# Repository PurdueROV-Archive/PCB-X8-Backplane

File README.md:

# PCB-X8-Backplane
The board to attach all boards. Note: May not actually be a backplane!
Here is another line!

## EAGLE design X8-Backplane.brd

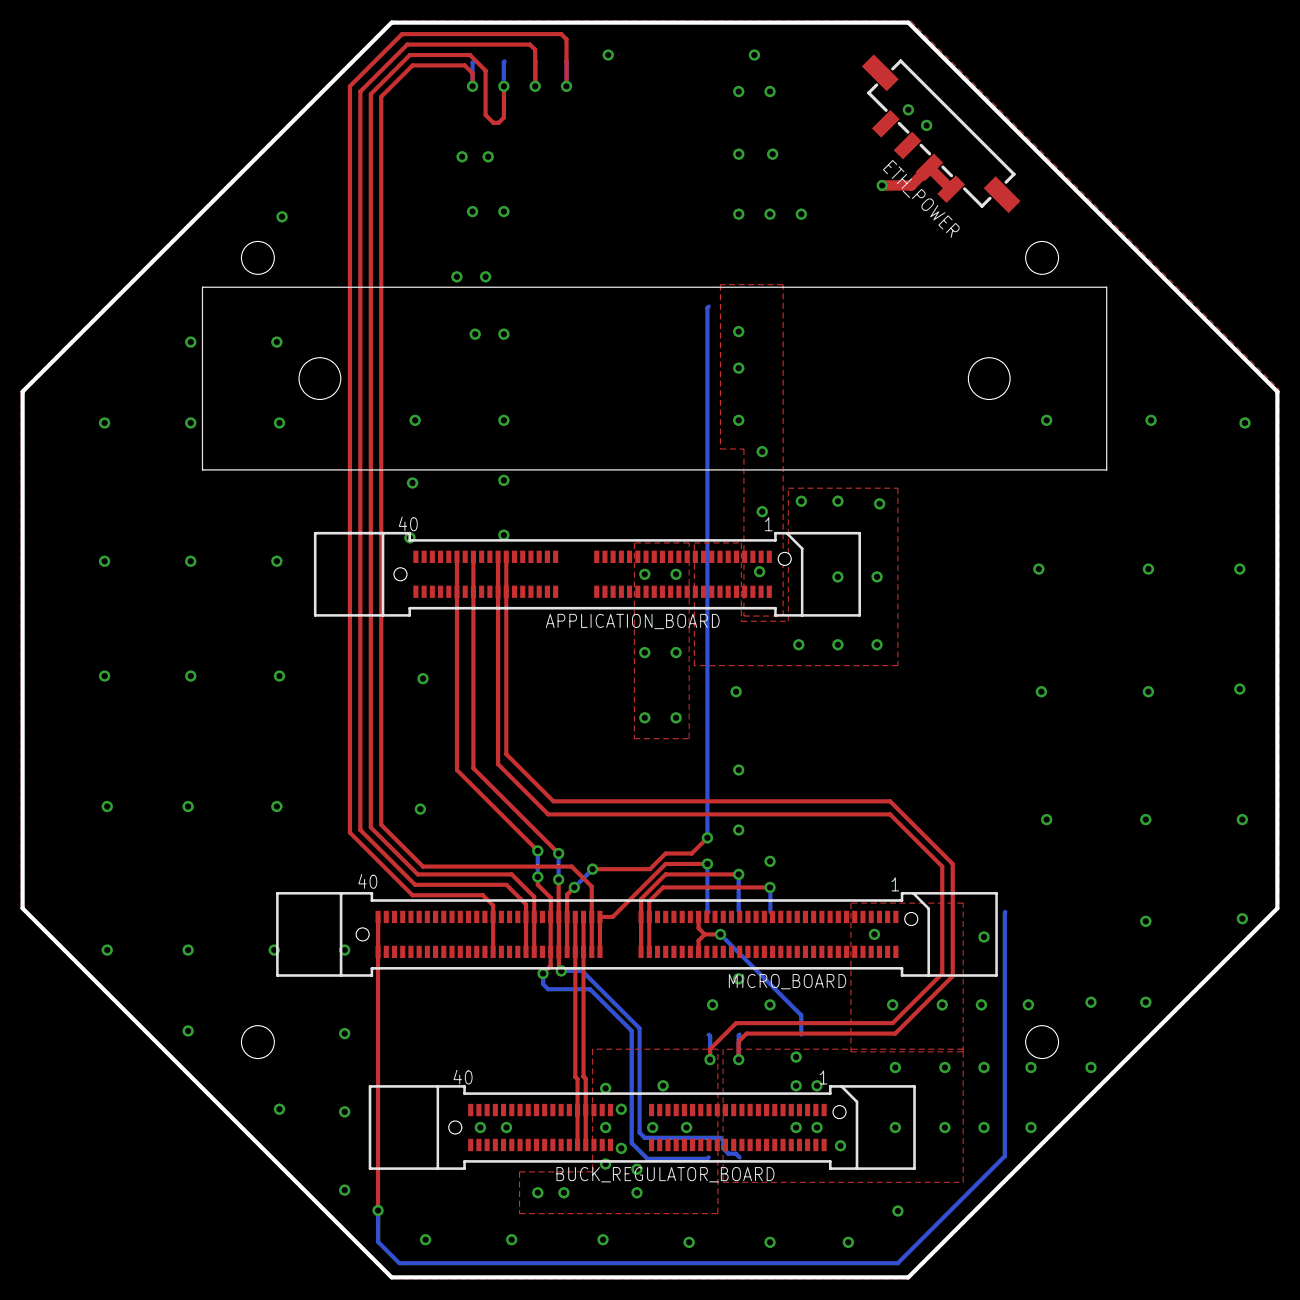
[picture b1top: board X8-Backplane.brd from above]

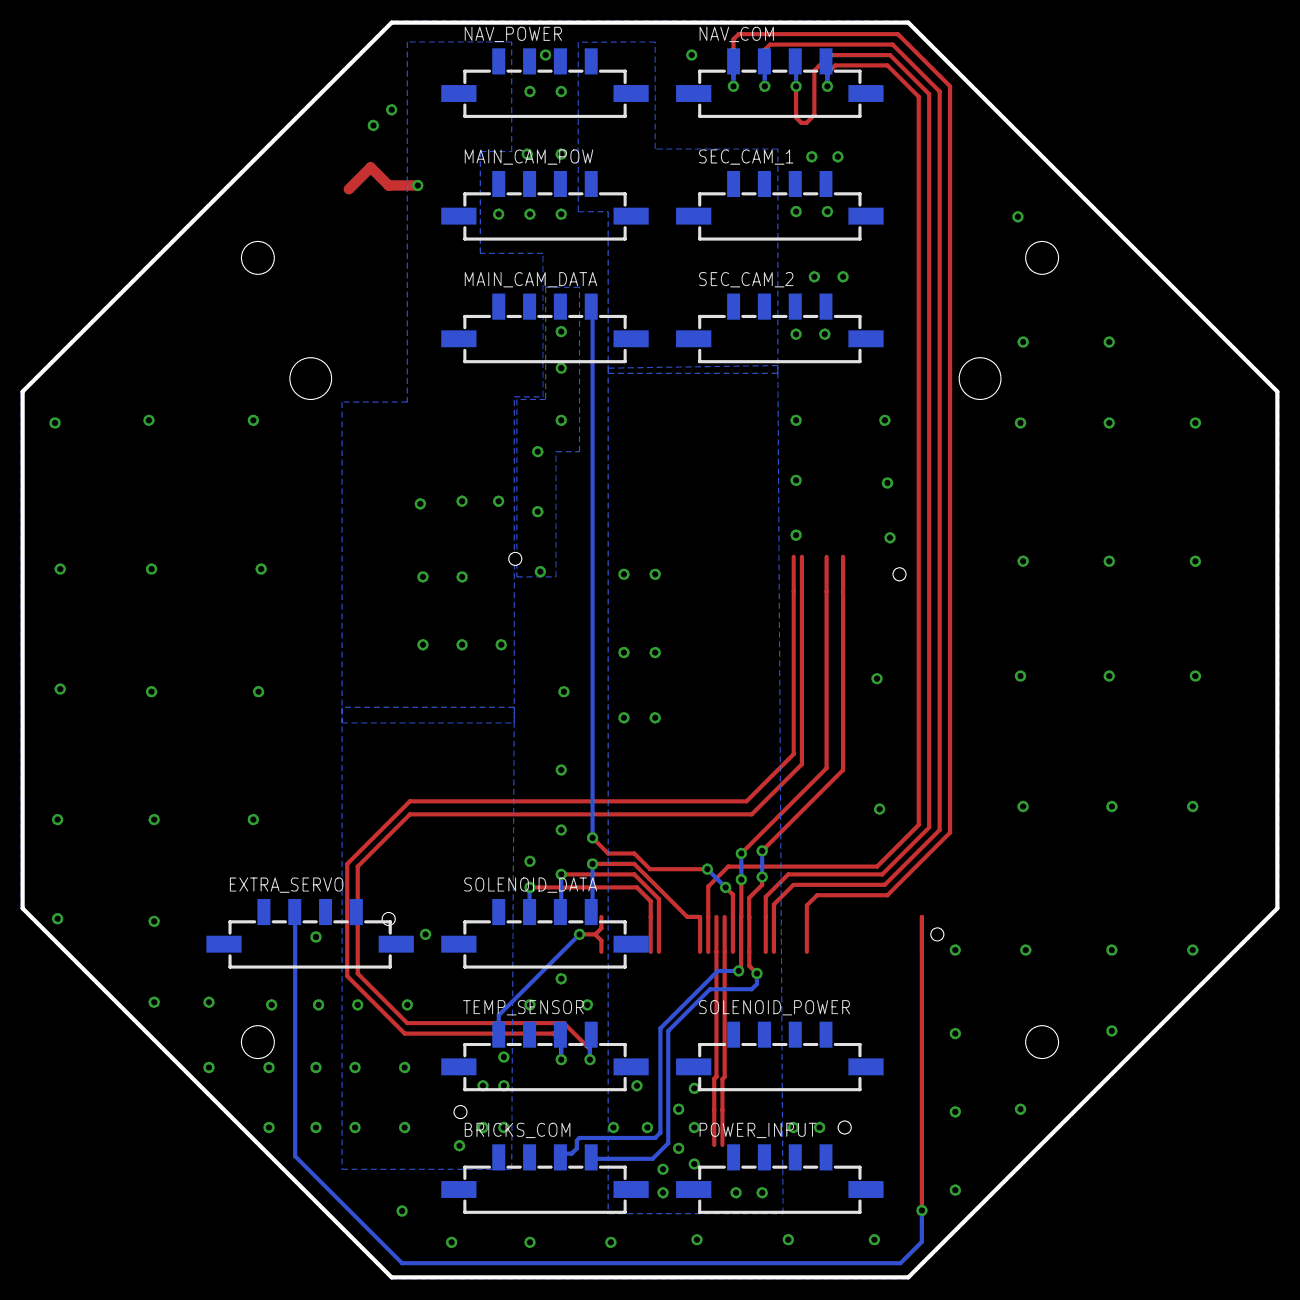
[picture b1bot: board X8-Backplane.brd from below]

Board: 2 copper layers, 122.1 x 122.1 mm, 17 parts (12 on the bottom side), 20 nets.

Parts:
APPLICATION_BOARD: HSEC8-140-01-XX-DV-A
BRICKS_COM: MICRO-FIT-4-SMD-PART; MICRO-FIT-4-SMD
BUCK_REGULATOR_BOARD: HSEC8-140-01-XX-DV-A
ETH_POWER: MICRO-FIT-4-SMD-PART; MICRO-FIT-4-SMD
EXTRA_SERVO: MICRO-FIT-4-SMD-PART; MICRO-FIT-4-SMD
MAIN_CAM_DATA: MICRO-FIT-4-SMD-PART; MICRO-FIT-4-SMD
MAIN_CAM_POW: MICRO-FIT-4-SMD-PART; MICRO-FIT-4-SMD
MICRO_BOARD: HSEC8-160-01-XX-DV-A
NAV_COM: MICRO-FIT-4-SMD-PART; MICRO-FIT-4-SMD
NAV_POWER: MICRO-FIT-4-SMD-PART; MICRO-FIT-4-SMD
POWER_INPUT: MICRO-FIT-4-SMD-PART; MICRO-FIT-4-SMD
SEC_CAM_1, SEC_CAM_2: MICRO-FIT-4-SMD-PART; MICRO-FIT-4-SMD
SOLENOID_DATA: MICRO-FIT-4-SMD-PART; MICRO-FIT-4-SMD
SOLENOID_POWER: MICRO-FIT-4-SMD-PART; MICRO-FIT-4-SMD
TEMP_SENSOR: MICRO-FIT-4-SMD-PART; MICRO-FIT-4-SMD
U$18: ETH_SWITCH

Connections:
+3V3: APPLICATION_BOARD.57, APPLICATION_BOARD.58, TEMP_SENSOR.C3
+5V: APPLICATION_BOARD.9, APPLICATION_BOARD.10, APPLICATION_BOARD.11, APPLICATION_BOARD.12, APPLICATION_BOARD.13, APPLICATION_BOARD.14, APPLICATION_BOARD.15, APPLICATION_BOARD.16, APPLICATION_BOARD.17, APPLICATION_BOARD.18, APPLICATION_BOARD.19, APPLICATION_BOARD.20, BUCK_REGULATOR_BOARD.1, BUCK_REGULATOR_BOARD.2, BUCK_REGULATOR_BOARD.3, BUCK_REGULATOR_BOARD.4, BUCK_REGULATOR_BOARD.5, BUCK_REGULATOR_BOARD.6, BUCK_REGULATOR_BOARD.7, BUCK_REGULATOR_BOARD.8, BUCK_REGULATOR_BOARD.9, BUCK_REGULATOR_BOARD.10, BUCK_REGULATOR_BOARD.11, BUCK_REGULATOR_BOARD.12, BUCK_REGULATOR_BOARD.13, BUCK_REGULATOR_BOARD.14, BUCK_REGULATOR_BOARD.15, BUCK_REGULATOR_BOARD.16, BUCK_REGULATOR_BOARD.17, BUCK_REGULATOR_BOARD.18, BUCK_REGULATOR_BOARD.19, BUCK_REGULATOR_BOARD.20, BUCK_REGULATOR_BOARD.21, BUCK_REGULATOR_BOARD.22, BUCK_REGULATOR_BOARD.23, BUCK_REGULATOR_BOARD.24, BUCK_REGULATOR_BOARD.25, BUCK_REGULATOR_BOARD.26, ETH_POWER.C1, ETH_POWER.C2, EXTRA_SERVO.C4, MAIN_CAM_DATA.C1, MAIN_CAM_DATA.C2, MICRO_BOARD.1, MICRO_BOARD.2, MICRO_BOARD.3, MICRO_BOARD.4, MICRO_BOARD.5, MICRO_BOARD.6, MICRO_BOARD.7, MICRO_BOARD.8, MICRO_BOARD.9, MICRO_BOARD.10, MICRO_BOARD.11, MICRO_BOARD.12, NAV_POWER.C1, SOLENOID_DATA.C1
+12V: APPLICATION_BOARD.21, APPLICATION_BOARD.22, APPLICATION_BOARD.23, APPLICATION_BOARD.24, APPLICATION_BOARD.25, APPLICATION_BOARD.26, APPLICATION_BOARD.27, APPLICATION_BOARD.28, APPLICATION_BOARD.29, APPLICATION_BOARD.30, APPLICATION_BOARD.31, APPLICATION_BOARD.32, APPLICATION_BOARD.33, APPLICATION_BOARD.34, BUCK_REGULATOR_BOARD.27, BUCK_REGULATOR_BOARD.28, BUCK_REGULATOR_BOARD.29, BUCK_REGULATOR_BOARD.30, BUCK_REGULATOR_BOARD.31, BUCK_REGULATOR_BOARD.32, BUCK_REGULATOR_BOARD.33, BUCK_REGULATOR_BOARD.34, BUCK_REGULATOR_BOARD.35, BUCK_REGULATOR_BOARD.36, BUCK_REGULATOR_BOARD.37, BUCK_REGULATOR_BOARD.38, BUCK_REGULATOR_BOARD.39, BUCK_REGULATOR_BOARD.40, BUCK_REGULATOR_BOARD.41, BUCK_REGULATOR_BOARD.42, BUCK_REGULATOR_BOARD.43, BUCK_REGULATOR_BOARD.44, BUCK_REGULATOR_BOARD.45, BUCK_REGULATOR_BOARD.46, BUCK_REGULATOR_BOARD.47, BUCK_REGULATOR_BOARD.48, BUCK_REGULATOR_BOARD.49, BUCK_REGULATOR_BOARD.50, MAIN_CAM_POW.C4, NAV_POWER.C4, POWER_INPUT.C1, POWER_INPUT.C2, SEC_CAM_1.C1, SEC_CAM_1.C2, SEC_CAM_2.C1, SEC_CAM_2.C2, SOLENOID_POWER.C1, SOLENOID_POWER.C2
BACK_UP_TEMP_DATA: MICRO_BOARD.49, MICRO_BOARD.50, TEMP_SENSOR.C1
BUCK_SCL: BUCK_REGULATOR_BOARD.53, BUCK_REGULATOR_BOARD.54, MICRO_BOARD.71, MICRO_BOARD.72
BUCK_SDA: BUCK_REGULATOR_BOARD.51, BUCK_REGULATOR_BOARD.52, MICRO_BOARD.69, MICRO_BOARD.70
CANH: APPLICATION_BOARD.69, APPLICATION_BOARD.70, BRICKS_COM.C4, MICRO_BOARD.77, MICRO_BOARD.78
CANL: APPLICATION_BOARD.65, APPLICATION_BOARD.66, BRICKS_COM.C3, MICRO_BOARD.75, MICRO_BOARD.76
CLK: MICRO_BOARD.63, MICRO_BOARD.64, SOLENOID_DATA.C3
DATA: MICRO_BOARD.65, MICRO_BOARD.66, SOLENOID_DATA.C4
ENABLE: MICRO_BOARD.61, MICRO_BOARD.62, SOLENOID_DATA.C2
GND: APPLICATION_BOARD.37, APPLICATION_BOARD.38, APPLICATION_BOARD.39, APPLICATION_BOARD.40, APPLICATION_BOARD.41, APPLICATION_BOARD.42, APPLICATION_BOARD.43, APPLICATION_BOARD.44, APPLICATION_BOARD.45, APPLICATION_BOARD.46, APPLICATION_BOARD.47, APPLICATION_BOARD.48, APPLICATION_BOARD.49, APPLICATION_BOARD.50, APPLICATION_BOARD.51, APPLICATION_BOARD.52, BUCK_REGULATOR_BOARD.55, BUCK_REGULATOR_BOARD.56, BUCK_REGULATOR_BOARD.57, BUCK_REGULATOR_BOARD.58, BUCK_REGULATOR_BOARD.59, BUCK_REGULATOR_BOARD.60, BUCK_REGULATOR_BOARD.61, BUCK_REGULATOR_BOARD.62, BUCK_REGULATOR_BOARD.63, BUCK_REGULATOR_BOARD.64, BUCK_REGULATOR_BOARD.65, BUCK_REGULATOR_BOARD.66, BUCK_REGULATOR_BOARD.67, BUCK_REGULATOR_BOARD.68, BUCK_REGULATOR_BOARD.69, BUCK_REGULATOR_BOARD.70, BUCK_REGULATOR_BOARD.71, BUCK_REGULATOR_BOARD.72, BUCK_REGULATOR_BOARD.73, BUCK_REGULATOR_BOARD.74, BUCK_REGULATOR_BOARD.75, BUCK_REGULATOR_BOARD.76, BUCK_REGULATOR_BOARD.77, BUCK_REGULATOR_BOARD.78, BUCK_REGULATOR_BOARD.79, BUCK_REGULATOR_BOARD.80, ETH_POWER.C3, ETH_POWER.C4, EXTRA_SERVO.C3, MAIN_CAM_POW.C1, MAIN_CAM_POW.C2, MAIN_CAM_POW.C3, MICRO_BOARD.21, MICRO_BOARD.22, MICRO_BOARD.23, MICRO_BOARD.24, MICRO_BOARD.25, MICRO_BOARD.26, MICRO_BOARD.27, MICRO_BOARD.28, MICRO_BOARD.29, MICRO_BOARD.30, MICRO_BOARD.31, MICRO_BOARD.32, MICRO_BOARD.33, MICRO_BOARD.34, MICRO_BOARD.35, MICRO_BOARD.36, NAV_POWER.C2, NAV_POWER.C3, POWER_INPUT.C3, POWER_INPUT.C4, SEC_CAM_1.C3, SEC_CAM_1.C4, SEC_CAM_2.C3, SEC_CAM_2.C4, SOLENOID_POWER.C3, SOLENOID_POWER.C4, TEMP_SENSOR.C2
LED_PWM: APPLICATION_BOARD.1, APPLICATION_BOARD.2, APPLICATION_BOARD.3, APPLICATION_BOARD.4, APPLICATION_BOARD.5, APPLICATION_BOARD.6, APPLICATION_BOARD.7, APPLICATION_BOARD.8, MAIN_CAM_DATA.C3
MAIN_SERVO: MAIN_CAM_DATA.C4, MICRO_BOARD.73, MICRO_BOARD.74
NAV_SCL: MICRO_BOARD.83, MICRO_BOARD.84, NAV_COM.C2
NAV_SDA: MICRO_BOARD.81, MICRO_BOARD.82, NAV_COM.C3
SECOND_SERVO: EXTRA_SERVO.C2, MICRO_BOARD.119, MICRO_BOARD.120
SONAR_DAC: MICRO_BOARD.91, MICRO_BOARD.92, NAV_COM.C1
SONAR_PWM: MICRO_BOARD.67, MICRO_BOARD.68, NAV_COM.C4
TEMP_DATA: APPLICATION_BOARD.59, APPLICATION_BOARD.60, TEMP_SENSOR.C4

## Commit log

2015-12-11 Rough sketch of the backplane
2015-12-12 Fleshing out the idea for the backplane
2015-12-15 Added more connections to the backplane
2015-12-29 Added more connectors to the backplane schematic
2016-01-01 First placement of parts
2016-01-01 Routed connections from micro board
2016-01-06 Changed around the order of the connectors
2016-01-06 Changed more connector lines
2016-01-09 Finished the backplane
2016-01-09 Moved the board into a valid location
2016-01-09 Made SCL and SDA lines of equal length
2016-01-11 added pikachu
2016-01-15 Added holes to to secure electronics if needed
2016-03-25 adding shift register eagle stuff
